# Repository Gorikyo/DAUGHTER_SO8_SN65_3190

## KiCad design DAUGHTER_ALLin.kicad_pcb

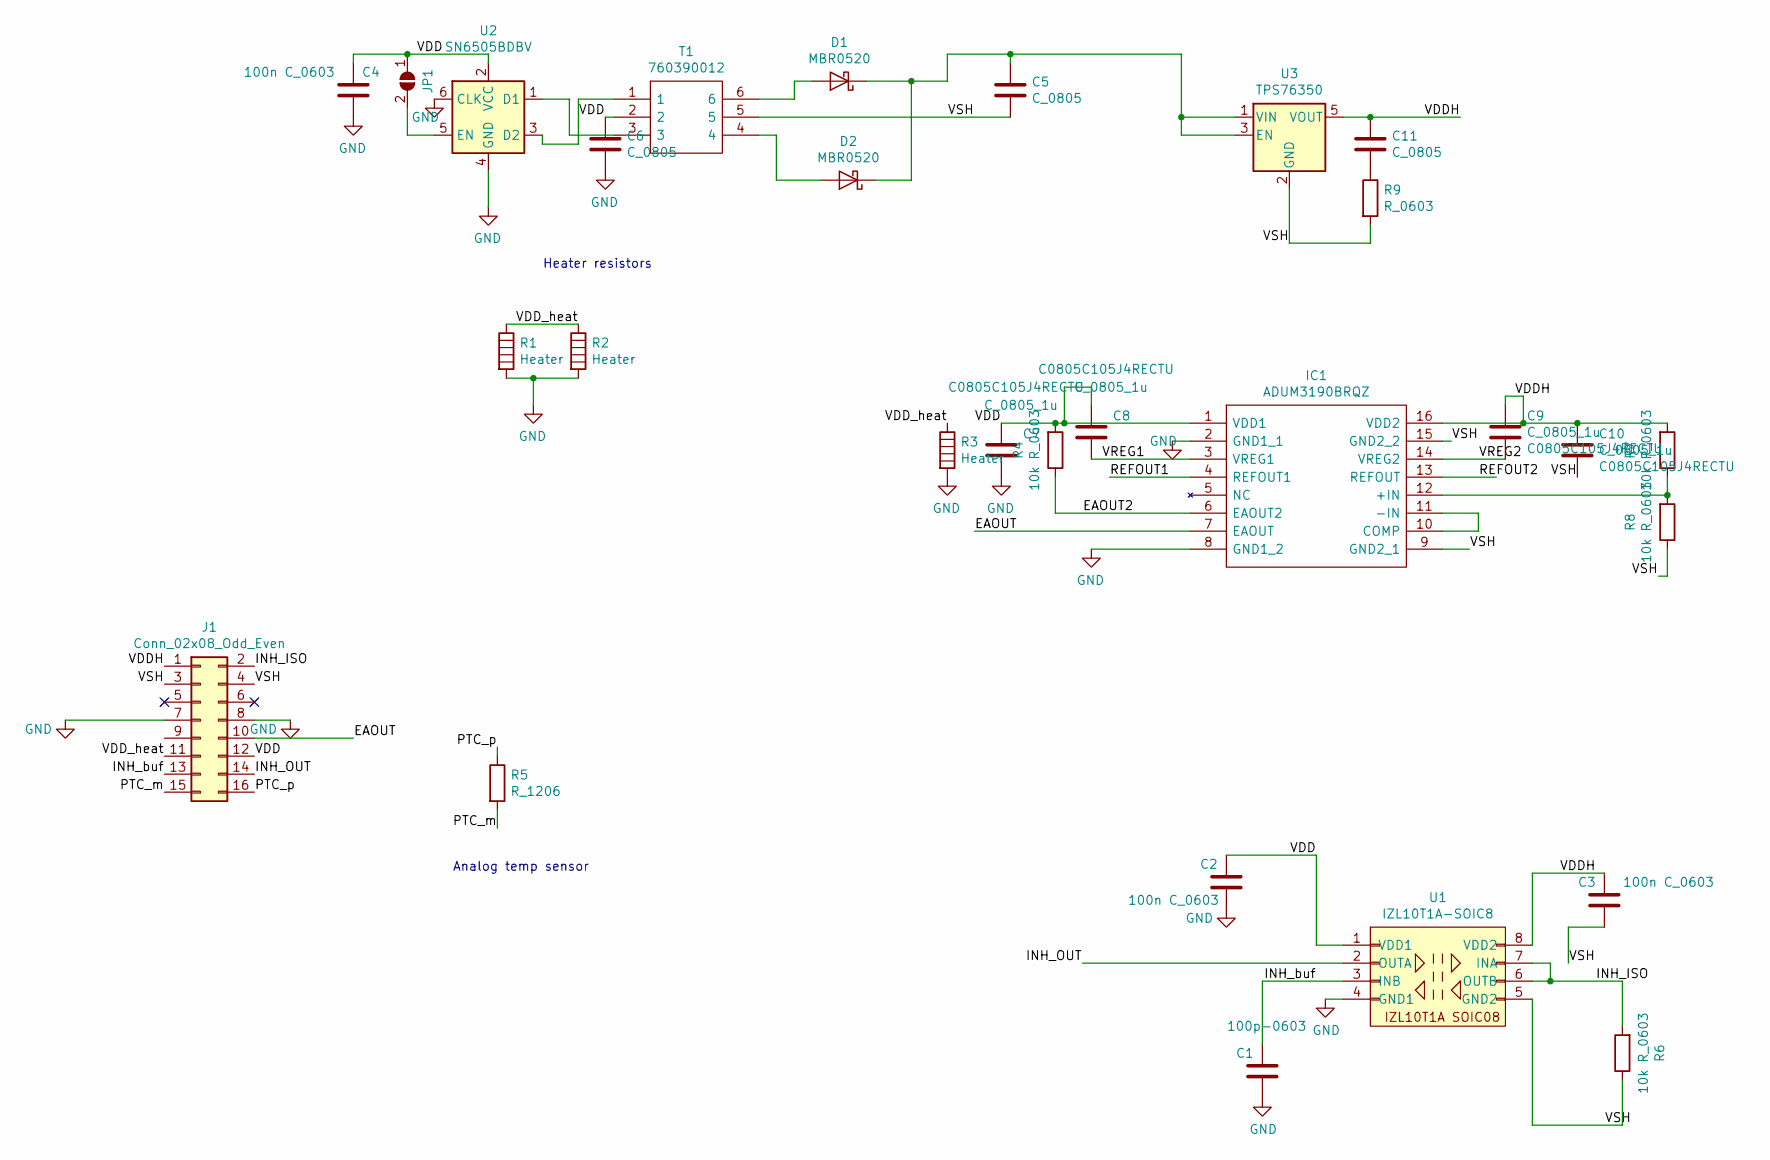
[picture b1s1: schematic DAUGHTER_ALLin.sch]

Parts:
C1: 100p-0603; C_0603_1608Metric
C2, C3, C4: 100n C_0603; C_0603_1608Metric
C5, C6, C11: C_0805; C_0805_2012Metric_Pad1.15x1.40mm_HandSolder
C7, C8, C9, C10: C_0805_1u; C_0805_2012Metric_Pad1.15x1.40mm_HandSolder; Manufacturer_Part_Number C0805C105J4RECTU
D1, D2: MBR0520; D_SOD-123
IC1: ADUM3190BRQZ; SOP64P600X175-16N; Manufacturer_Part_Number ADUM3190BRQZ; Mouser Part Number 584-ADUM3190BRQZ
J1: Conn_02x08_Odd_Even; PinHeader_2x08_P2.54mm_Horizontal
JP1: SolderJumper_2_Open_VDDTECH; SolderJumper-2_P1.3mm_Open_RoundedPad1.0x1.5mm
R1, R2, R3: Heater; R_2010_5025Metric_Pad1.52x2.65mm_HandSolder
R4, R6, R7, R8: 10k R_0603; R_0603_1608Metric
R5: R_1206; R_1206_3216Metric_Pad1.42x1.75mm_HandSolder
R9: R_0603; R_0603_1608Metric_Pad1.05x0.95mm_HandSolder
T1: 760390012; 760390015; Mouser Part Number 710-760390012
U1: IZL10T1A-SOIC8; SOIC8_typ_HEAT_no_vias
U2: SN6505BDBV; SOT-23-6
U3: TPS76350; SOT-23-5

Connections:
/EAOUT: IC1.7 (EAOUT), J1.10
/EAOUT2: IC1.6 (EAOUT2), R4.1
/INH_ISO: J1.2, R6.2, U1.6 (OUTB), U1.7 (INA)
/INH_OUT: J1.14, U1.2 (OUTA)
/INH_buf: C1.1, J1.13, U1.3 (INB)
/PTC_m: J1.15, R5.2
/PTC_p: J1.16, R5.1
/REFOUT1: IC1.4 (REFOUT1)
/REFOUT2: IC1.13 (REFOUT)
/VDD: C2.1, C4.1, C6.1, C7.1, C8.1, IC1.1 (VDD1), J1.12, JP1.1 (A), R4.2, T1.2, U1.1 (VDD1), U2.2 (VCC)
/VDDH: C3.1, C9.1, C10.1, C11.1, IC1.16 (VDD2), J1.1, R7.2, U1.8 (VDD2), U3.5 (VOUT)
/VDD_heat: J1.11, R1.1, R2.1, R3.1
/VREG1: C8.2, IC1.3 (VREG1)
/VREG2: C9.2, IC1.14 (VREG2)
/VSH: C3.2, C5.2, C10.2, IC1.9 (GND2_1), IC1.15 (GND2_2), J1.3, J1.4, R6.1, R8.1, R9.2, T1.5, U1.5 (GND2), U3.2 (GND)
GND: C1.2, C2.2, C4.2, C6.2, C7.2, IC1.2 (GND1_1), IC1.8 (GND1_2), J1.7, J1.8, R1.2, R2.2, R3.2, U1.4 (GND1), U2.4 (GND), U2.6 (CLK)
unnamed: C5.1, D1.1 (K), D2.1 (K), U3.1 (VIN), U3.3 (EN)
unnamed: C11.2, R9.1
unnamed: D1.2 (A), T1.6
unnamed: D2.2 (A), T1.4
unnamed: IC1.10 (COMP), IC1.11 (-IN)
unnamed: IC1.12 (+IN), R7.1, R8.2
unnamed: JP1.2 (B), U2.5 (EN)
unnamed: T1.1, U2.3 (D2)
unnamed: T1.3, U2.1 (D1)

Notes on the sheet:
Analog temp sensor
Heater resistors

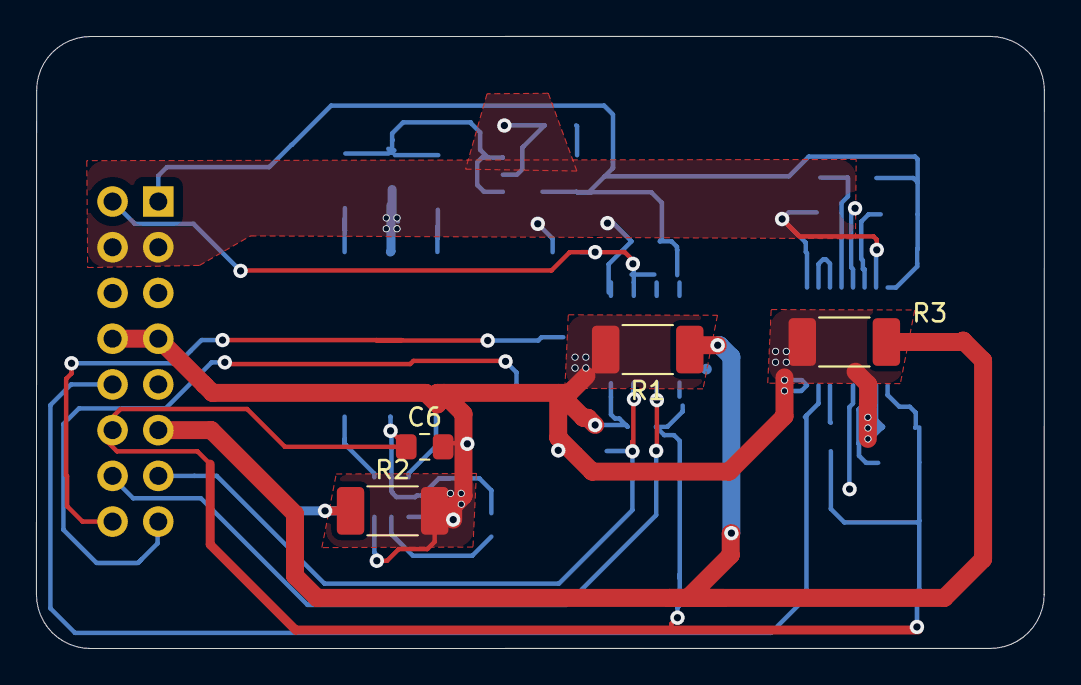
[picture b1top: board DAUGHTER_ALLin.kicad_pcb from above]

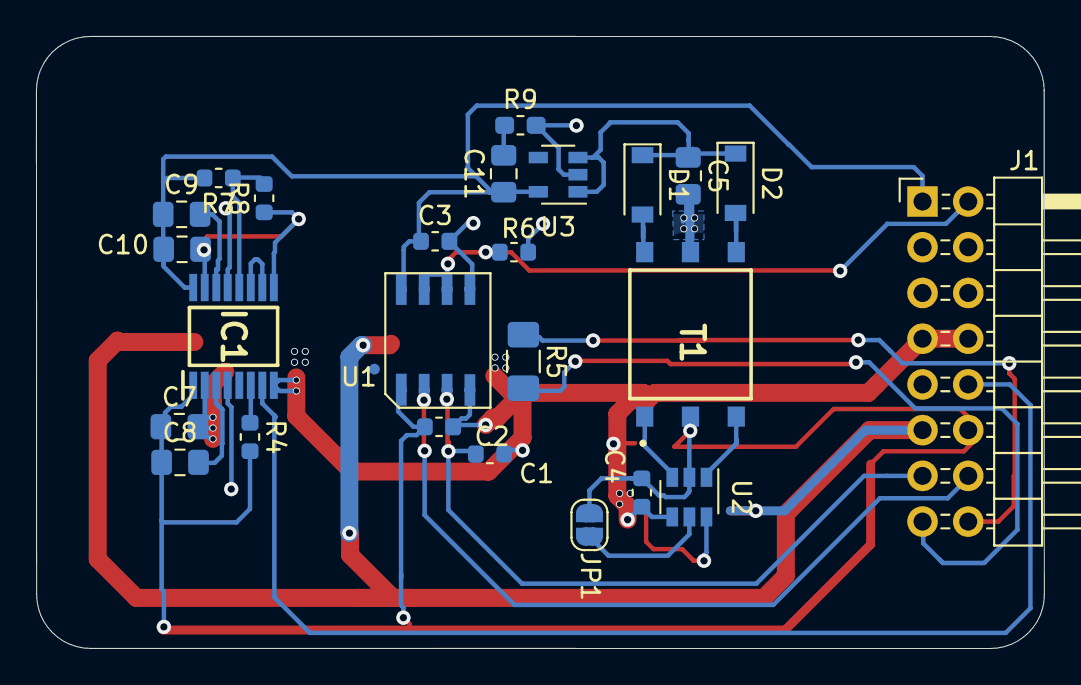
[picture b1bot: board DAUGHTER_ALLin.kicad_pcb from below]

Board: 2 copper layers, 56.0 x 34.0 mm, 29 parts (25 on the bottom side), 23 nets.

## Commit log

2021-01-19 initial commit based on SN6501 daughter
2021-01-26 multicb version
